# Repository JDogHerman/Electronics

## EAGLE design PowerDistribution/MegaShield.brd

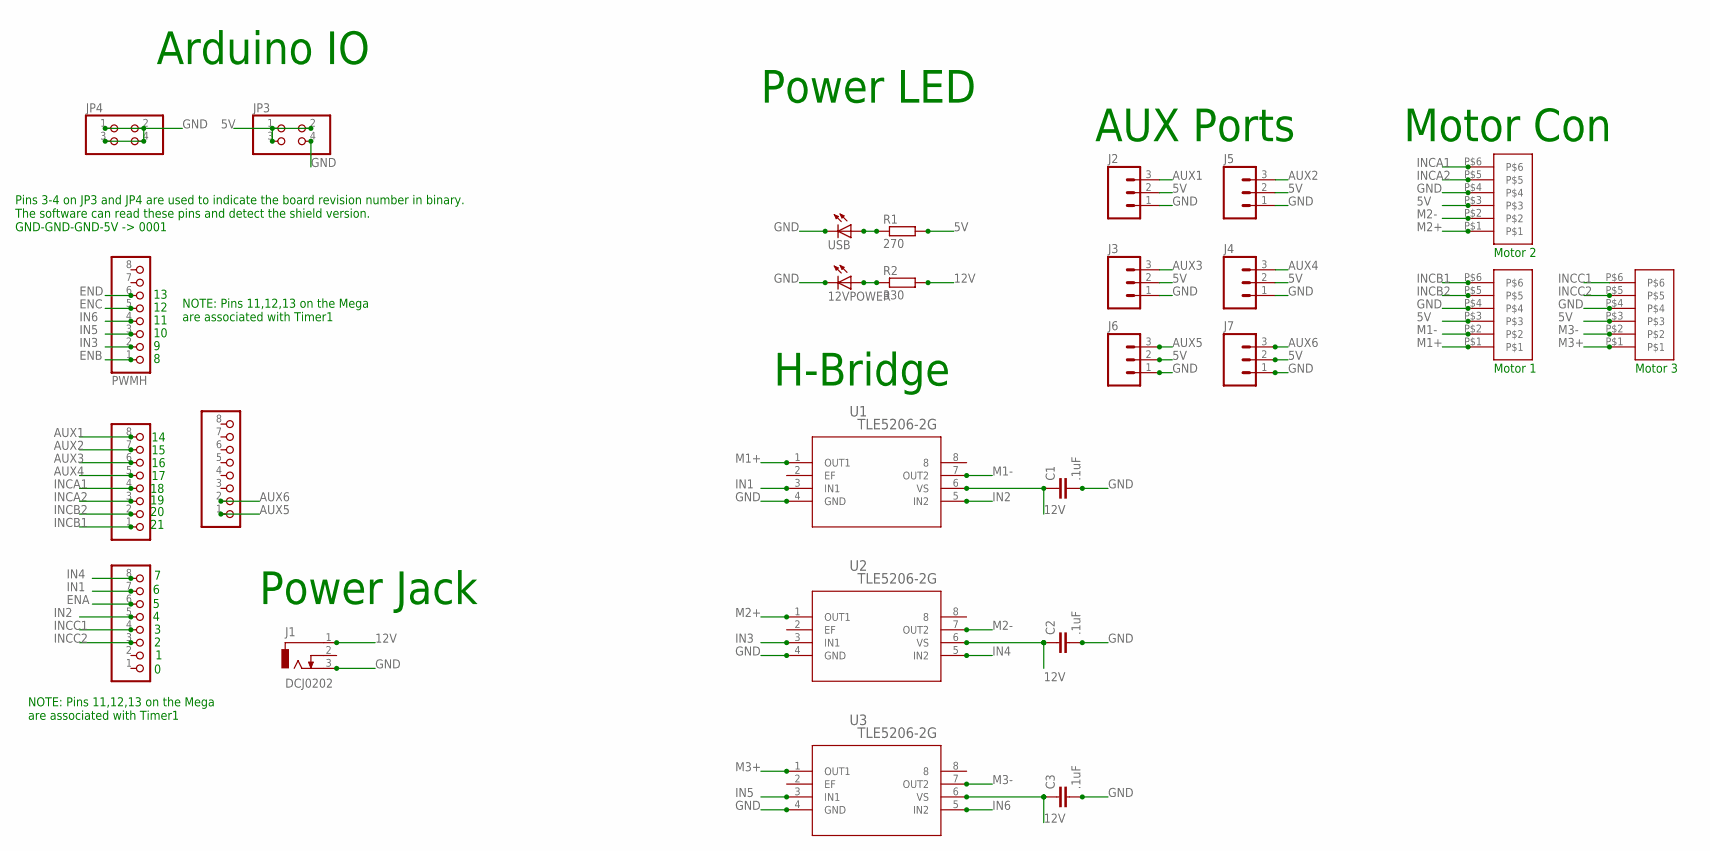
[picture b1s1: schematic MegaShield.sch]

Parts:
12VPOWER: LED_E; LED_1206
C1, C2, C3: .1uF; C0805
COMMUNICATION, COMMUNICATION1: PINHD-1X8; 1X08
J1: DCJ0202
J2, J3, J4, J5, J6, J7: M03LOCK; 1X03_LOCK
JP3, JP4: PINHD-2X2; 2X02
PWMH: PINHD-1X8; 1X08
PWML: PINHD-1X8; 1X08
R1: 270; R0805
R2: 330; R0805
U1, U2, U3: TLE5206-2G; PG-TO263-7
U$1, U$12, U$20: JST-PH-6; JST-PHR-6-SMD
USB: LED_E; LED_1206

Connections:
5V: J2.2, J3.2, J4.2, J5.2, J6.2, J7.2, JP3.1, JP3.2, JP3.3, R1.2, U$1.P$3, U$12.P$3, U$20.P$3
12V: C1.1, C2.1, C3.1, J1.1, R2.2, U1.6 (VS), U2.6 (VS), U3.6 (VS)
AUX1: COMMUNICATION.8, J2.3
AUX2: COMMUNICATION.7, J5.3
AUX3: COMMUNICATION.6, J3.3
AUX4: COMMUNICATION.5, J4.3
AUX5: COMMUNICATION1.1, J6.3
AUX6: COMMUNICATION1.2, J7.3
ENA: PWML.6
ENB: PWMH.1
ENC: PWMH.5
END: PWMH.6
GND: 12VPOWER.C, C1.2, C2.2, C3.2, J1.3, J2.1, J3.1, J4.1, J5.1, J6.1, J7.1, JP3.4, JP4.1, JP4.2, JP4.3, JP4.4, U1.4 (GND), U2.4 (GND), U3.4 (GND), U$1.P$4, U$12.P$4, U$20.P$4, USB.C
IN1: PWML.7, U1.3 (IN1)
IN2: PWML.5, U1.5 (IN2)
IN3: PWMH.2, U2.3 (IN1)
IN4: PWML.8, U2.5 (IN2)
IN5: PWMH.3, U3.3 (IN1)
IN6: PWMH.4, U3.5 (IN2)
INCA1: COMMUNICATION.4, U$12.P$6
INCA2: COMMUNICATION.3, U$12.P$5
INCB1: COMMUNICATION.1, U$1.P$6
INCB2: COMMUNICATION.2, U$1.P$5
INCC1: PWML.4, U$20.P$6
INCC2: PWML.3, U$20.P$5
M1+: U1.1 (OUT1), U$1.P$1
M1-: U1.7 (OUT2), U$1.P$2
M2+: U2.1 (OUT1), U$12.P$1
M2-: U2.7 (OUT2), U$12.P$2
M3+: U3.1 (OUT1), U$20.P$1
M3-: U3.7 (OUT2), U$20.P$2
unnamed: R1.1, USB.A
unnamed: 12VPOWER.A, R2.1

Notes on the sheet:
Motor 1
Motor 2
H-Bridge
Power LED
Power Jack
Arduino IO
AUX Ports
Motor Con
Motor 3
Pins 3-4 on JP3 and JP4 are used to indicate the board revision number in binary. The software can read these pins and detect the shield version. GND-GND-GND-5V -> 0001
NOTE: Pins 11,12,13 on the Mega are associated with Timer1

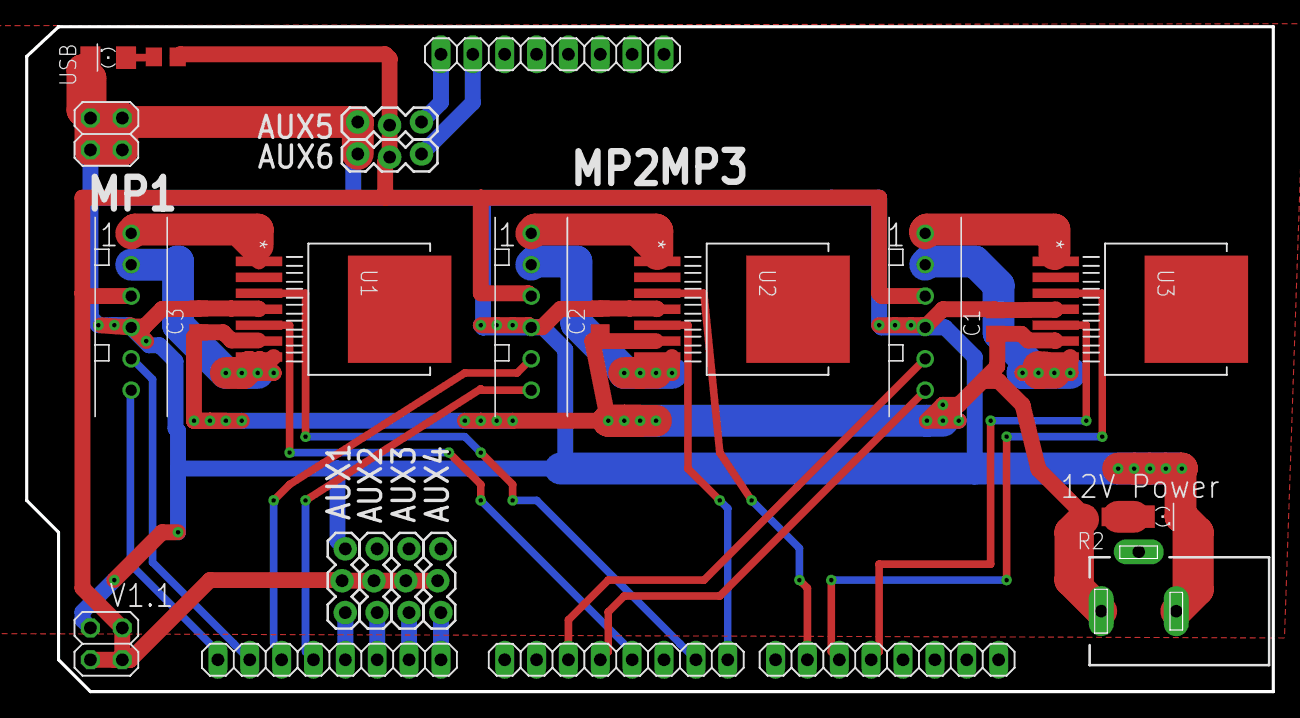
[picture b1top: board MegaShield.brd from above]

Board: 2 copper layers, 99.4 x 53.0 mm, 26 parts (0 on the bottom side), 29 nets.

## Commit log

2017-09-10 New Board Design built on TLE5206-2G
    First revision of branch design using TLE5206-2G
    https://www.digikey.com/products/en?keywords=TLE5206-2GCT-ND
2017-09-10 More Power Vias
    @blurfl recommended more vias for a higher current capacity. Each power leg has at lease 4 Vias
2017-09-11 Now with more Power Vias
    @blurfl recommended more vias for a higher current capacity. Each 12v+GND power leg has at least 4 Vias

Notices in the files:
parts and their libraries:
SparkFun-Connectors: Licensing: Creative Commons ShareAlike 4.0 International - https://creativecommons.org/licenses/by-sa/4.0
